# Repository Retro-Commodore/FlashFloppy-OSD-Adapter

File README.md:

# FlashFloppy-OSD-Adapter
 Adapter which should make it a little easier to handle the bluepill for regular GOTEK drives for the Amiga
 
# What is it?
It's just a basic adapter which draws out the pins needed to connect the bluepill with the Amiga and GOTEK drive.
You can also program the Bluepill using this adapter. 
 
# How to use
Download the gerber (zip) file and upload it to your favorite PCB manufacturer. I'm using jlcpcb.com.

Check out this image and use the link below for reference

Go to https://github.com/keirf/FF_OSD 

You decide if you want to use sil headers or just solder wires to the holes.
If you have a 3D Printet drive bay, you can attach the Adapter with Bluepill to here.

# Do I really need this?
No, you can use the Bluepill without this adapter.

# More?
You can isolate the bottom, with i.e. cardboard/hotglue, or isolation tape, to prevent accidently shorts.

# Placements
The resistor values are printet on the silkscreen, which isn't visible on the picture above.

# Parts list
2 x 4,7k Ohm throughhole resistor

1 x 270  Ohm throughhole resistor

2 x 1x4 pin SIL header male - you can ommit these if you want to solder wires directly and program before installing

2 x 1x2 pin SIL header male - you can ommit these if you want to solder wires directly

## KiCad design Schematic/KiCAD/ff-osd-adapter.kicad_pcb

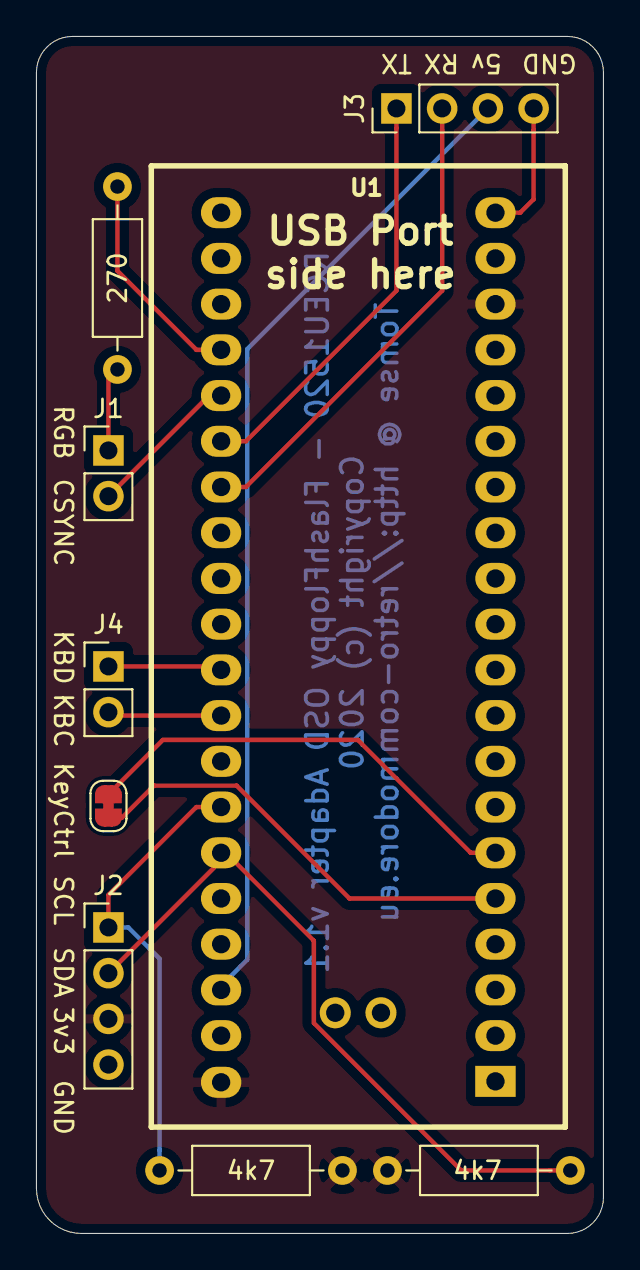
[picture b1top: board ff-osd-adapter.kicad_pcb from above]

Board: 2 copper layers, 31.5 x 66.5 mm, 9 parts (0 on the bottom side), 14 nets.

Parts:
J1: Amiga_Video; PinHeader_1x02_P2.54mm_Vertical
J2: GOTEK; PinHeader_1x04_P2.54mm_Vertical
J3: Programming; PinHeader_1x04_P2.54mm_Vertical
J4: Amiga_Keyboard; PinHeader_1x02_P2.54mm_Vertical
KeyCtrl: Amiga_Key_Input_To_FF; SolderJumper-2_P1.3mm_Bridged_RoundedPad1.0x1.5mm
R1: 270; R_Axial_DIN0207_L6.3mm_D2.5mm_P10.16mm_Horizontal
R2, R3: 4k7; R_Axial_DIN0207_L6.3mm_D2.5mm_P10.16mm_Horizontal
U1: BluePill_STM32F103C

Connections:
+3V3: J2.3, R2.1, R3.1, U1.18, U1.40
/5v: J3.3, U1.38
/CSYNC: J1.2, U1.25
/KB_CLOCK: J4.2, U1.32
/KB_DATA: J4.1, U1.31
/RGB: J1.1, R1.1
/RX: J3.2, U1.27
/SCL: J2.1, R3.2, U1.34
/SDA: J2.2, R2.2, U1.35
/TX: J3.1, U1.26
GND: J2.4, J3.4, U1.19, U1.20, U1.39
unnamed: KeyCtrl.1, U1.5
unnamed: KeyCtrl.2, U1.6
unnamed: R1.2, U1.24

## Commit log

2020-03-16 Initial release
    Version 1.0 of the FlashFloppy adapter
2020-03-16 Create FlashFloppy-OSD-Adapter.png
    Added pcb image
2020-03-17 Create FlashFloppy-OSD-Adapter_pcb.png
    adding pcb image for documentation
2020-04-06 Cosmetic Changes
2020-04-08 Fixing connection colors
2020-12-23 Cosmetic changes/corrections
2020-12-23 v1.1 - added support for Amiga Keyboard disk change control

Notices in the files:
Schematic/KiCAD/ff-osd-adapter.kicad_pcb:
Copyright (C) Tomse 2020
Copyright (c) 2020
